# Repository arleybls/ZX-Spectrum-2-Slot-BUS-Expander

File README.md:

# ZX-Spectrum-2Slot-BUS-Expander

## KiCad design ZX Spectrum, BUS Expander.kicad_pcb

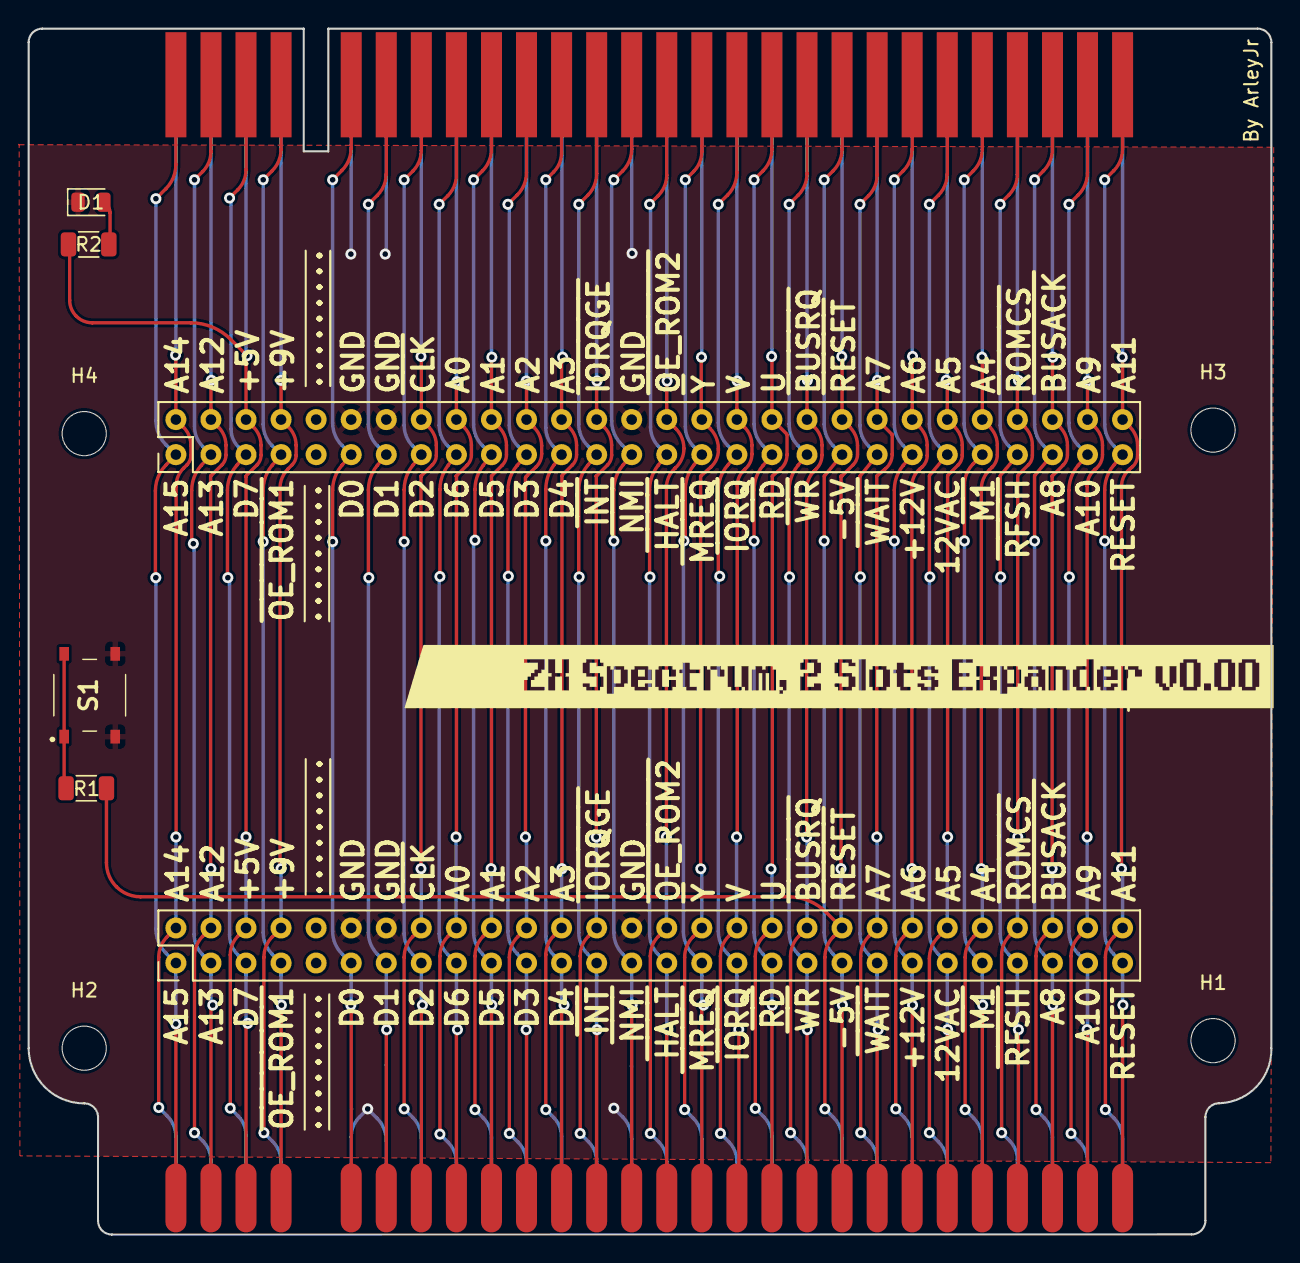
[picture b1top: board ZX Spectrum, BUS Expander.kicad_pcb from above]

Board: 2 copper layers, 90.0 x 87.4 mm, 13 parts (0 on the bottom side), 54 nets.

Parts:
D1: LED; LED_0805_2012Metric
H1, H2, H3, H4: MountingHole; MountingHole_3.2mm_M3
J1, J2: Conn_02x28_Row_Letter_First; ZX Bus Socket
R1: 100R; R_1206_3216Metric
R2: 330R; R_1206_3216Metric
S1: PTS526_SM15_SMTR2_LFS; PTS526SM15SMTR2LFS
Z1: EDGE; ZX Bus, Edge
Z2: PASS-THROUGH; ZX Bus, Edge Pass-T
kibuzzard-65E37D50: G***; kibuzzard-65E37D50

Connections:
12VAC: J1.A23 (Pin_a23), J2.A23 (Pin_a23), Z1.A23 (12VAC), Z2.A23 (12VAC)
+5V: J1.B3 (Pin_b3), J2.B3 (Pin_b3), R2.1, Z1.B3 (+5v), Z2.B3 (+5v)
+9V: J1.B4 (Pin_b4), J2.B4 (Pin_b4), Z1.B4 (+9V), Z2.B4 (+9V)
+12V: J1.A22 (Pin_a22), J2.A22 (Pin_a22), Z1.A22 (+12V), Z2.A22 (+12V)
-5V: J1.A20 (Pin_a20), J2.A20 (Pin_a20), Z1.A20 (-5V), Z2.A20 (-5V)
A0: J1.B9 (Pin_b9), J2.B9 (Pin_b9), Z1.B9 (A0), Z2.B9 (A0)
A1: J1.B10 (Pin_b10), J2.B10 (Pin_b10), Z1.B10 (A1), Z2.B10 (A1)
A2: J1.B11 (Pin_b11), J2.B11 (Pin_b11), Z1.B11 (A2), Z2.B11 (A2)
A3: J1.B12 (Pin_b12), J2.B12 (Pin_b12), Z1.B12 (A3), Z2.B12 (A3)
A4: J1.B24 (Pin_b24), J2.B24 (Pin_b24), Z1.B24 (A4), Z2.B24 (A4)
A5: J1.B23 (Pin_b23), J2.B23 (Pin_b23), Z1.B23 (A5), Z2.B23 (A5)
A6: J1.B22 (Pin_b22), J2.B22 (Pin_b22), Z1.B22 (A6), Z2.B22 (A6)
A7: J1.B21 (Pin_b21), J2.B21 (Pin_b21), Z1.B21 (A7), Z2.B21 (A7)
A8: J1.A26 (Pin_a26), J2.A26 (Pin_a26), Z1.A26 (A8), Z2.A26 (A8)
A9: J1.B27 (Pin_b27), J2.B27 (Pin_b27), Z1.B27 (A9), Z2.B27 (A9)
A10: J1.A27 (Pin_a27), J2.A27 (Pin_a27), Z1.A27 (A10), Z2.A27 (A10)
A11: J1.B28 (Pin_b28), J2.B28 (Pin_b28), Z1.B28 (A11), Z2.B28 (A11)
A12: J1.B2 (Pin_b2), J2.B2 (Pin_b2), Z1.B2 (A12), Z2.B2 (A12)
A13: J1.A2 (Pin_a2), J2.A2 (Pin_a2), Z1.A2 (A13), Z2.A2 (A13)
A14: J1.B1 (Pin_b1), J2.B1 (Pin_b1), Z1.B1 (A14), Z2.B1 (A14)
A15: J1.A1 (Pin_a1), J2.A1 (Pin_a1), Z1.A1 (A15), Z2.A1 (A15)
D0: J1.A6 (Pin_a6), J2.A6 (Pin_a6), Z1.A6 (D0), Z2.A6 (D0)
D1: J1.A7 (Pin_a7), J2.A7 (Pin_a7), Z1.A7 (D1), Z2.A7 (D1)
D2: J1.A8 (Pin_a8), J2.A8 (Pin_a8), Z1.A8 (D2), Z2.A8 (D2)
D3: J1.A11 (Pin_a11), J2.A11 (Pin_a11), Z1.A11 (D3), Z2.A11 (D3)
D4: J1.A12 (Pin_a12), J2.A12 (Pin_a12), Z1.A12 (D4), Z2.A12 (D4)
D5: J1.A10 (Pin_a10), J2.A10 (Pin_a10), Z1.A10 (D5), Z2.A10 (D5)
D6: J1.A9 (Pin_a9), J2.A9 (Pin_a9), Z1.A9 (D6), Z2.A9 (D6)
D7: J1.A3 (Pin_a3), J2.A3 (Pin_a3), Z1.A3 (D7), Z2.A3 (D7)
GND: D1.1 (K), J1.B6 (Pin_b6), J1.B7 (Pin_b7), J1.B14 (Pin_b14), J2.B6 (Pin_b6), J2.B7 (Pin_b7), J2.B14 (Pin_b14), S1.3 (NO_1), S1.4 (NO_2), Z1.B6 (GND), Z1.B7 (GND), Z1.B14 (GND), Z2.B6 (GND), Z2.B7 (GND), Z2.B14 (GND)
unnamed: D1.2 (A), R2.2
unnamed: R1.1, S1.1 (COM_1), S1.2 (COM_2)
RESET/NC: J1.A28 (Pin_a28), J2.A28 (Pin_a28), Z1.A28 (RESET), Z2.A28 (RESET)
U: J1.B18 (Pin_b18), J2.B18 (Pin_b18), Z1.B18 (U), Z2.B18 (U)
V: J1.B17 (Pin_b17), J2.B17 (Pin_b17), Z1.B17 (V), Z2.B17 (V)
~BUSACK: J1.B26 (Pin_b26), J2.B26 (Pin_b26), Z1.B26 (~BUSACK), Z2.B26 (~BUSACK)
~BUSRQ: J1.B19 (Pin_b19), J2.B19 (Pin_b19), Z1.B19 (~BUSRQ), Z2.B19 (~BUSRQ)
~CLK: J1.B8 (Pin_b8), J2.B8 (Pin_b8), Z1.B8 (~CLK), Z2.B8 (~CLK)
~HALT: J1.A15 (Pin_a15), J2.A15 (Pin_a15), Z1.A15 (~HALT), Z2.A15 (~HALT)
~INT: J1.A13 (Pin_a13), J2.A13 (Pin_a13), Z1.A13 (~INT), Z2.A13 (~INT)
~IORQGE: J1.B13 (Pin_b13), J2.B13 (Pin_b13), Z1.B13 (~IORQGE), Z2.B13 (~IORQGE)
~IORQ: J1.A17 (Pin_a17), J2.A17 (Pin_a17), Z1.A17 (~IORQ), Z2.A17 (~IORQ)
~M1: J1.A24 (Pin_a24), J2.A24 (Pin_a24), Z1.A24 (~M1), Z2.A24 (~M1)
~MREQ: J1.A16 (Pin_a16), J2.A16 (Pin_a16), Z1.A16 (~MREQ), Z2.A16 (~MREQ)
~NMI: J1.A14 (Pin_a14), J2.A14 (Pin_a14), Z1.A14 (~NMI), Z2.A14 (~NMI)
~OEM_ROM1: J1.A4 (Pin_a4), J2.A4 (Pin_a4), Z1.A4 (~OEM_ROM1), Z2.A4 (~OEM_ROM1)
~OE_ROM2/VIDEO: J1.B15 (Pin_b15), J2.B15 (Pin_b15), Z1.B15 (~OE_ROM2), Z2.B15 (~OE_ROM2)
~RD: J1.A18 (Pin_a18), J2.A18 (Pin_a18), Z1.A18 (~RD), Z2.A18 (~RD)
~RESET: J1.B20 (Pin_b20), J2.B20 (Pin_b20), R1.2, Z1.B20 (~RESET), Z2.B20 (~RESET)
~RFSH: J1.A25 (Pin_a25), J2.A25 (Pin_a25), Z1.A25 (~RFSH), Z2.A25 (~RFSH)
~ROMCS: J1.B25 (Pin_b25), J2.B25 (Pin_b25), Z1.B25 (~ROMCS), Z2.B25 (~ROMCS)
~WAIT: J1.A21 (Pin_a21), J2.A21 (Pin_a21), Z1.A21 (~WAIT), Z2.A21 (~WAIT)
~WR: J1.A19 (Pin_a19), J2.A19 (Pin_a19), Z1.A19 (~WR), Z2.A19 (~WR)
~Y: J1.B16 (Pin_b16), J2.B16 (Pin_b16), Z1.B16 (~Y), Z2.B16 (~Y)

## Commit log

2024-04-05 ibom added
2024-04-13 Sche + Render
